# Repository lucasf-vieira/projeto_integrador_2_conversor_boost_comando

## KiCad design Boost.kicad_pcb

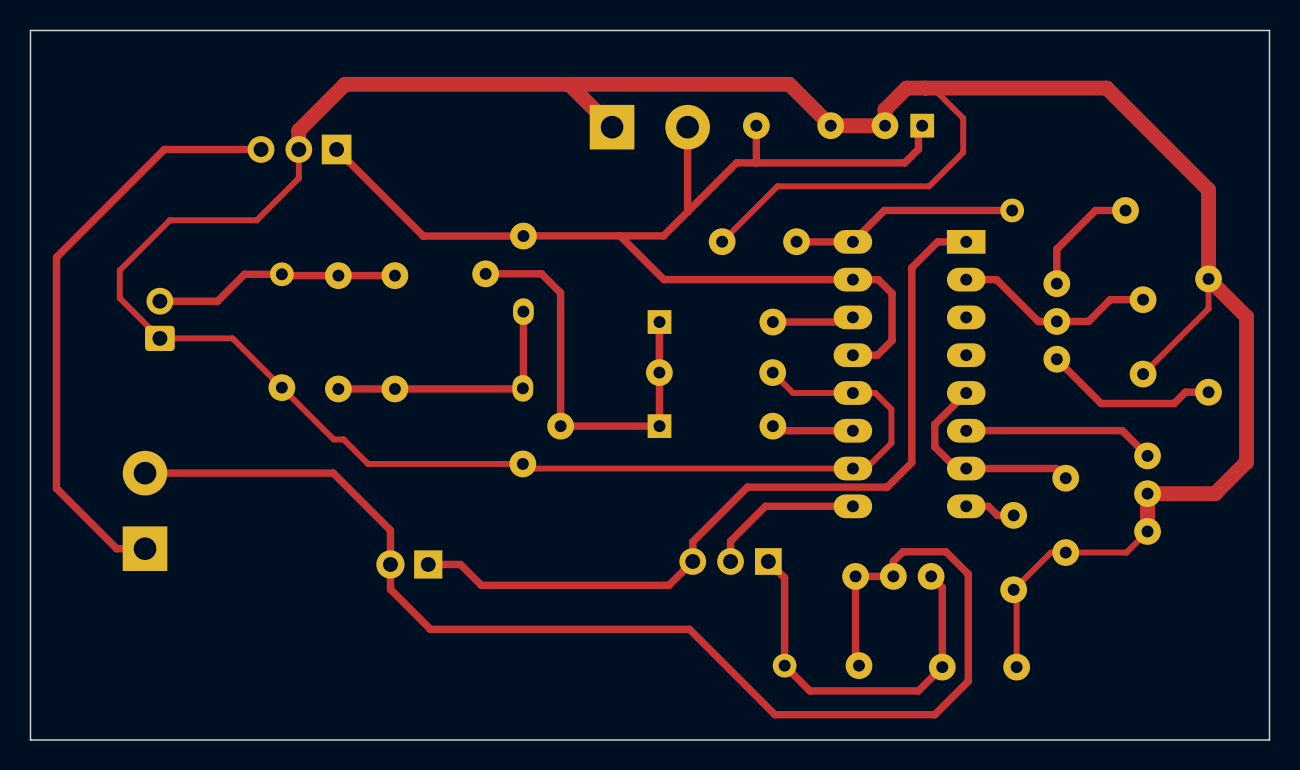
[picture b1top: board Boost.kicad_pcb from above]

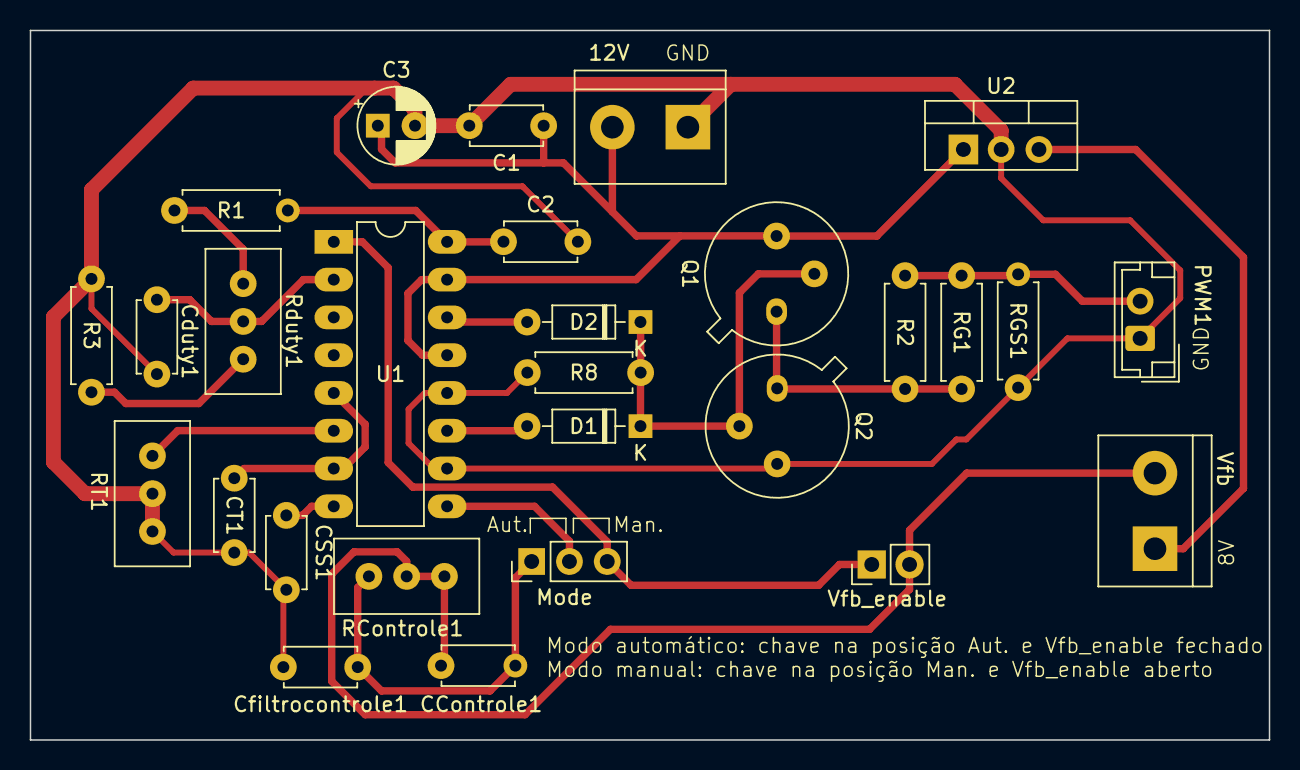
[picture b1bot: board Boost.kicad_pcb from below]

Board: 2 copper layers, 83.3 x 47.7 mm, 28 parts (28 on the bottom side), 19 nets.

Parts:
12V: Alimentação; TerminalBlock_bornier-2_P5.08mm
C1, C2: 100 nF; C_Disc_D4.7mm_W2.5mm_P5.00mm
C3: 10 uF; CP_Radial_D5.0mm_P2.00mm
CControle1: CControle; C_Disc_D4.7mm_W2.5mm_P5.00mm
CSS1: 39 nF; C_Disc_D4.7mm_W2.5mm_P5.00mm
CT1: 2,2 nF; C_Disc_D4.7mm_W2.5mm_P5.00mm
Cduty1: 100 pF; C_Disc_D4.7mm_W2.5mm_P5.00mm
Cfiltrocontrole1: C5; C_Disc_D4.7mm_W2.5mm_P5.00mm
D1, D2: D; D_DO-35_SOD27_P7.62mm_Horizontal
Mode: MODO; PinHeader_1x03_P2.54mm_Vertical
PWM1: Conn_01x02_Pin; JST_EH_B2B-EH-A_1x02_P2.50mm_Vertical
Q1: 2N2222; TO-39-3
Q2: 2N2907; TO-39-3
R1, R3, R8: 10 K; R_Axial_DIN0207_L6.3mm_D2.5mm_P7.62mm_Horizontal
R2: R; R_Axial_DIN0207_L6.3mm_D2.5mm_P7.62mm_Horizontal
RControle1: 47 K; Potentiometer_Bourns_3296W_Vertical
RG1: 8,76R; R_Axial_DIN0207_L6.3mm_D2.5mm_P7.62mm_Horizontal
RGS1: 10 K; R_Axial_DIN0207_L6.3mm_D2.5mm_P7.62mm_Horizontal
RT1: 47 K; Potentiometer_Bourns_3296W_Vertical
Rduty1: 47 K; Potentiometer_Bourns_3296W_Vertical
U1: SG3525; CERDIP-16_W7.62mm_SideBrazed_LongPads
U2: LM7808_TO220; TO-220-3_Vertical
Vfb: Vfb; TerminalBlock_bornier-2_P5.08mm
Vfb_enable: Feedback_enable; PinHeader_1x02_P2.54mm_Vertical

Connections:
GNDREF: 12V.1, C1.2, C2.2, C3.2, CSS1.2, CT1.2, Cduty1.2, Cfiltrocontrole1.2, PWM1.1, Q2.3 (C), R3.1, R8.2, RGS1.1, RT1.1, RT1.2, U1.10 (SD), U1.12 (GND), U2.2 (GND)
unnamed: D1.2 (A), U1.11 (OUTA)
unnamed: D1.1 (K), D2.1 (K), Q1.2 (B), Q2.2 (B), R8.1
unnamed: D2.2 (A), U1.14 (OUTB)
unnamed: U2.3 (VO), Vfb.1
unnamed: CControle1.2, Cfiltrocontrole1.1, Mode.1 (A), RControle1.1
unnamed: Mode.3 (B), U1.1 (INV), Vfb_enable.1 (A)
unnamed: Mode.2 (C), U1.9 (COMP)
unnamed: PWM1.2, R2.2, RG1.2, RGS1.2
unnamed: Q1.1 (E), Q2.1 (E), R2.1, RG1.1
unnamed: R1.1, Rduty1.3
unnamed: R3.2, Rduty1.1
unnamed: CT1.1, U1.5 (CT), U1.7 (DISCH)
unnamed: Cduty1.1, Rduty1.2, U1.2 (NI)
unnamed: RT1.3, U1.6 (RT)
unnamed: CSS1.1, U1.8 (SS)
VCC: 12V.2, C1.1, C3.1, Q1.3 (C), U1.13 (VC), U1.15 (VIN), U2.1 (VI)
VREF: C2.1, R1.2, U1.16 (REF)
Vfb: CControle1.1, RControle1.2, RControle1.3, Vfb.2, Vfb_enable.2 (B)

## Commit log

2024-11-11 Adição dos arquivos do projeto
2024-11-11 Remoção das zonas de cobre
